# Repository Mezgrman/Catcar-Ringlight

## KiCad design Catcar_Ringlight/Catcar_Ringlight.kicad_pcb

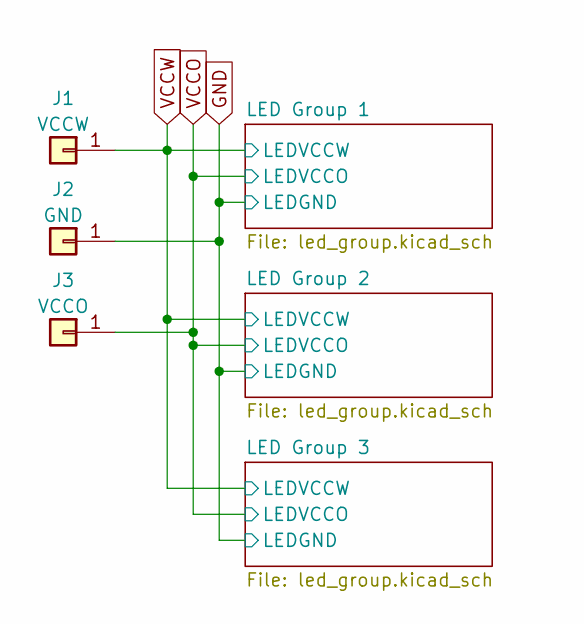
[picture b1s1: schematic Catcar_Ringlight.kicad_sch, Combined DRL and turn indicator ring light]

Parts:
J1: VCCW; TestPoint_Pad_1.5x1.5mm
J2: GND; TestPoint_Pad_1.5x1.5mm
J3: VCCO; TestPoint_Pad_1.5x1.5mm

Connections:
GND: J2.1; also elsewhere on the board
VCCO: J3.1; also elsewhere on the board
VCCW: J1.1; also elsewhere on the board

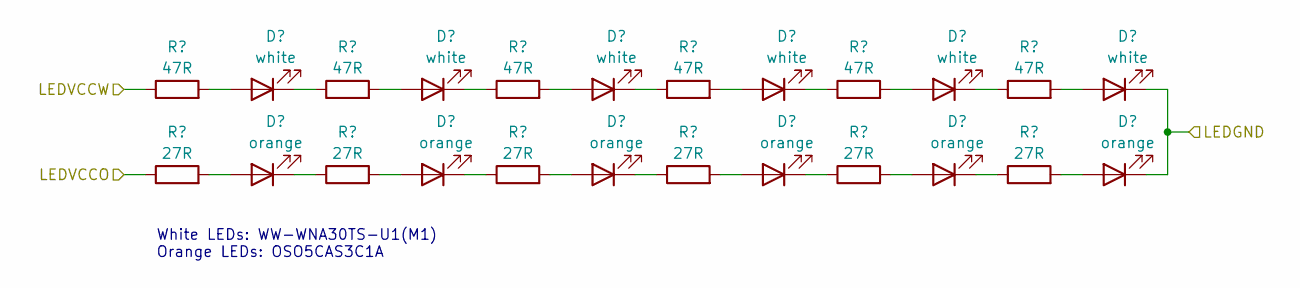
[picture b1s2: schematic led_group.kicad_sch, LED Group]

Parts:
D1, D2, D3, D4, D5, D6: white; LED_3528_2pin
D7, D8, D9, D10, D11, D12: orange; LED_3528_4pin
R1, R2, R3, R4, R5, R6: 47R; R_1206_3216Metric
R7, R8, R9, R10, R11, R12: 27R; R_1206_3216Metric

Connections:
GND: D6.1 (K), D12.1 (K); also elsewhere on the board
unnamed: D1.2 (A), R1.2
unnamed: D1.1 (K), R2.1
unnamed: D2.2 (A), R2.2
unnamed: D2.1 (K), R3.1
unnamed: D3.2 (A), R3.2
unnamed: D3.1 (K), R4.1
unnamed: D4.2 (A), R4.2
unnamed: D4.1 (K), R5.1
unnamed: D5.2 (A), R5.2
unnamed: D5.1 (K), R6.1
unnamed: D6.2 (A), R6.2
unnamed: D7.2 (A), R7.2
unnamed: D7.1 (K), R8.1
unnamed: D8.2 (A), R8.2
unnamed: D8.1 (K), R9.1
unnamed: D9.2 (A), R9.2
unnamed: D9.1 (K), R10.1
unnamed: D10.2 (A), R10.2
unnamed: D10.1 (K), R11.1
unnamed: D11.2 (A), R11.2
unnamed: D11.1 (K), R12.1
unnamed: D12.2 (A), R12.2
VCCO: R7.1; also elsewhere on the board
VCCW: R1.1; also elsewhere on the board

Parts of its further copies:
D13, D14, D15, D16, D17, D18, D25, D26, D27, D28, D29, D30: white; LED_3528_2pin
D19, D20, D21, D22, D23, D24, D31, D32, D33, D34, D35, D36: orange; LED_3528_4pin
R13, R14, R15, R16, R17, R18, R25, R26, R27, R28, R29, R30: 47R; R_1206_3216Metric
R19, R20, R21, R22, R23, R24, R31, R32, R33, R34, R35, R36: 27R; R_1206_3216Metric

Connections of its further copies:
GND: D18.1 (K), D24.1 (K), D30.1 (K), D36.1 (K); also elsewhere on the board
unnamed: D13.2 (A), R13.2
unnamed: D13.1 (K), R14.1
unnamed: D14.2 (A), R14.2
unnamed: D14.1 (K), R15.1
unnamed: D15.2 (A), R15.2
unnamed: D15.1 (K), R16.1
unnamed: D16.2 (A), R16.2
unnamed: D16.1 (K), R17.1
unnamed: D17.2 (A), R17.2
unnamed: D17.1 (K), R18.1
unnamed: D18.2 (A), R18.2
unnamed: D19.2 (A), R19.2
unnamed: D19.1 (K), R20.1
unnamed: D20.2 (A), R20.2
unnamed: D20.1 (K), R21.1
unnamed: D21.2 (A), R21.2
unnamed: D21.1 (K), R22.1
unnamed: D22.2 (A), R22.2
unnamed: D22.1 (K), R23.1
unnamed: D23.2 (A), R23.2
unnamed: D23.1 (K), R24.1
unnamed: D24.2 (A), R24.2
unnamed: D25.2 (A), R25.2
unnamed: D25.1 (K), R26.1
unnamed: D26.2 (A), R26.2
unnamed: D26.1 (K), R27.1
unnamed: D27.2 (A), R27.2
unnamed: D27.1 (K), R28.1
unnamed: D28.2 (A), R28.2
unnamed: D28.1 (K), R29.1
unnamed: D29.2 (A), R29.2
unnamed: D29.1 (K), R30.1
unnamed: D30.2 (A), R30.2
unnamed: D31.2 (A), R31.2
unnamed: D31.1 (K), R32.1
unnamed: D32.2 (A), R32.2
unnamed: D32.1 (K), R33.1
unnamed: D33.2 (A), R33.2
unnamed: D33.1 (K), R34.1
unnamed: D34.2 (A), R34.2
unnamed: D34.1 (K), R35.1
unnamed: D35.2 (A), R35.2
unnamed: D35.1 (K), R36.1
unnamed: D36.2 (A), R36.2
VCCO: R19.1, R31.1; also elsewhere on the board
VCCW: R13.1, R25.1; also elsewhere on the board

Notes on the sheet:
White LEDs: WW-WNA30TS-U1(M1) Orange LEDs: OSO5CAS3C1A

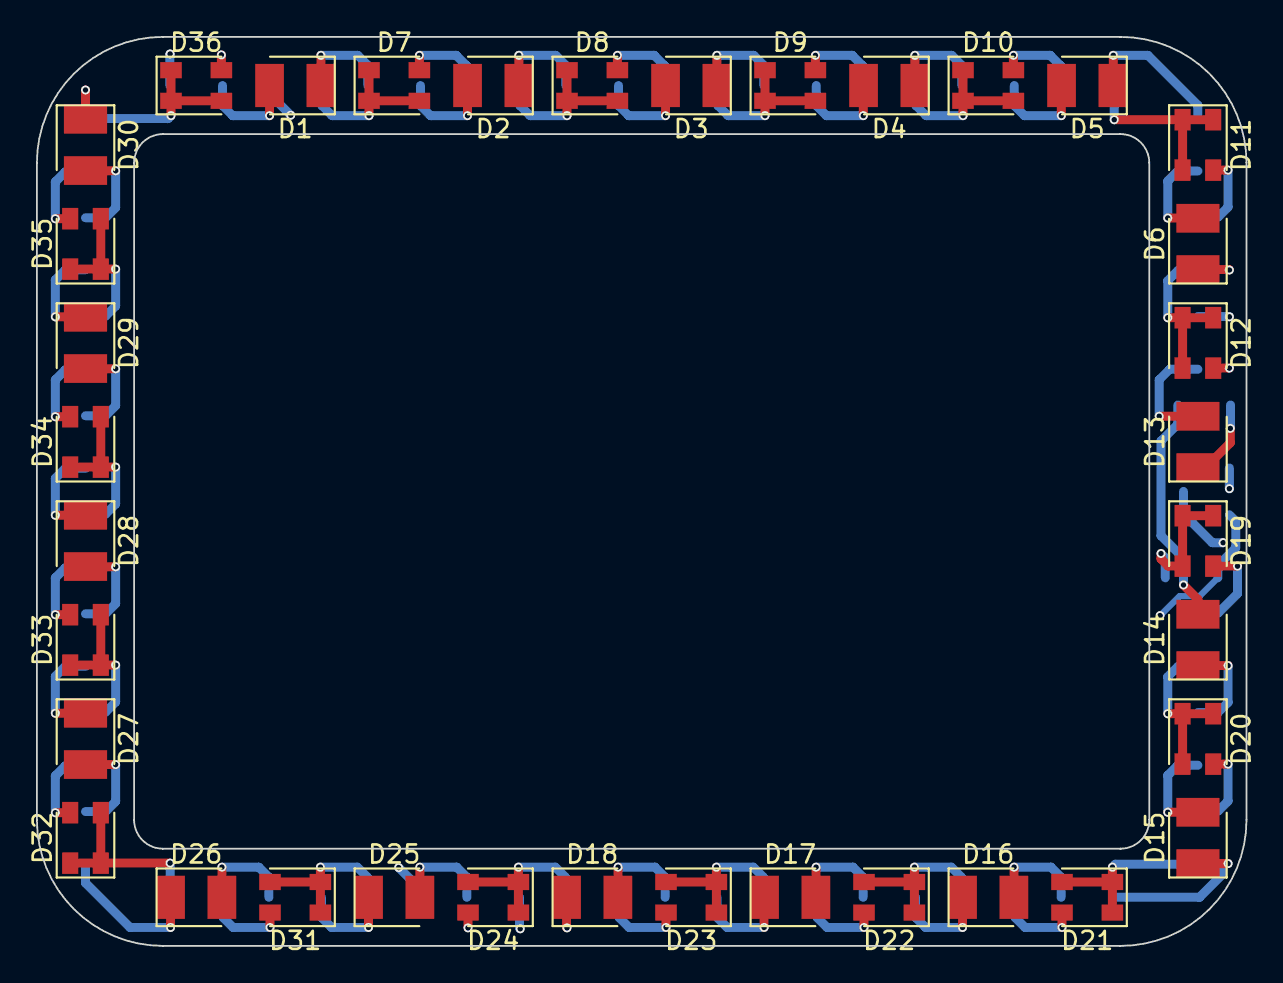
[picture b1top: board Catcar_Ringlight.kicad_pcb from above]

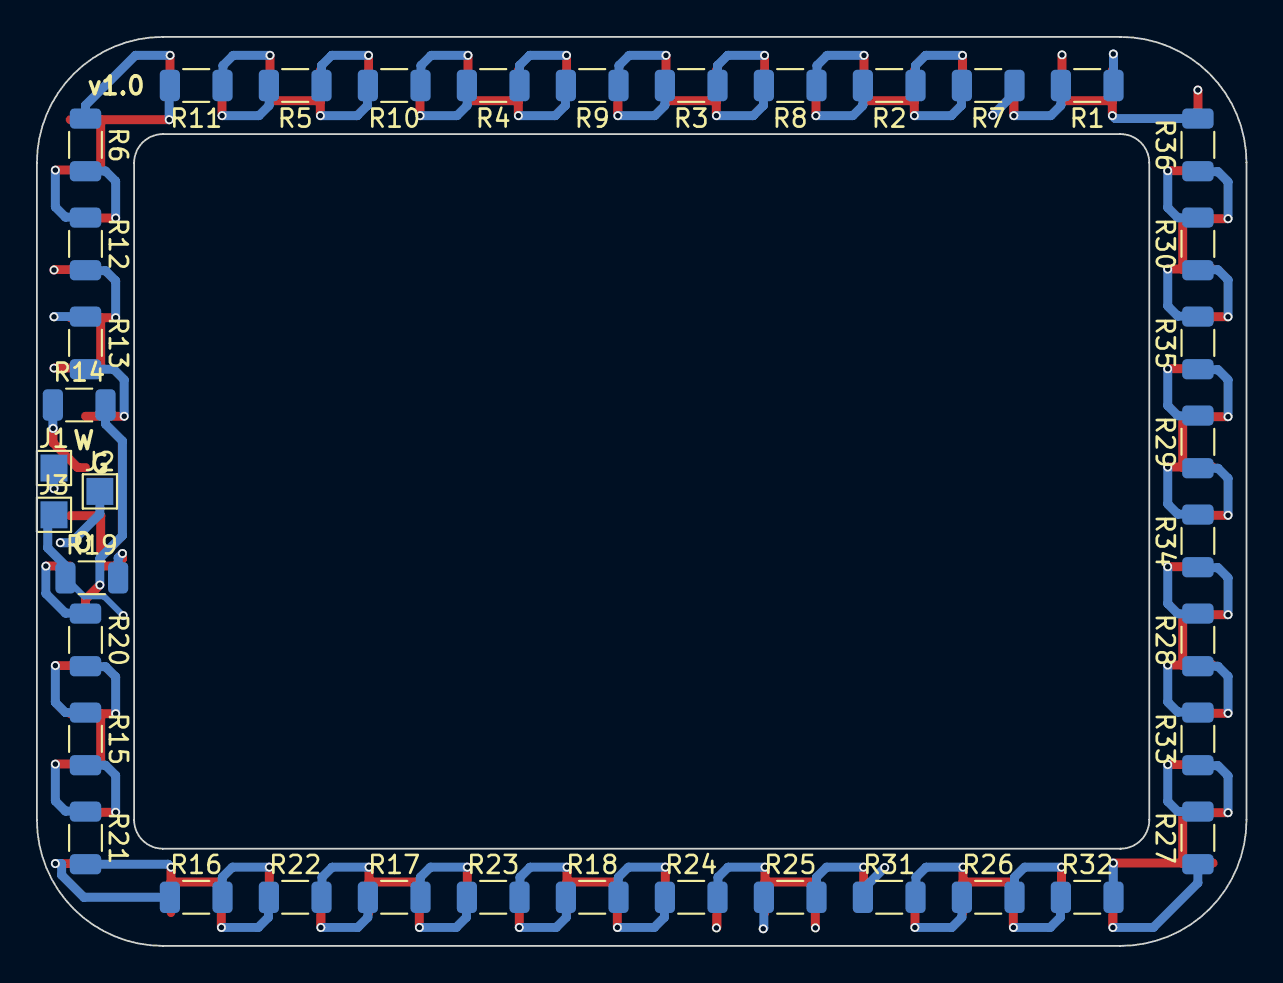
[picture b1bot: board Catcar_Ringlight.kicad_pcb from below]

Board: 4 copper layers, 67.2 x 50.5 mm, 75 parts (39 on the bottom side), 69 nets.

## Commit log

2023-08-02 Change orange LED type
